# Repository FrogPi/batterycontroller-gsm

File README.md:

# GSM Battery Box Monitoring and Control Board

Electrial Engineering Final Year Project Deliverable

Charith Amarasinghe 2012 <ca508@ic.ac.uk>

## Features

* 1x Metered 12V Input/Output (Battery Connection)
* 2x Metered 12V Input/Outputs (Device Connection) with 4x IO pins each
* 1x 5V/3A USB Compliant Output
* Integrated SIMCOM SIM900 GSM Modem with U.FL Antenna Connector
* SPI interface for nRF24L01 RF module
* Integrated SIM and MicroSD socket
* RTCC Battery Backup
* PIC24FJ256GB106 Microcontroller with PICKit3 debug port
* microUSB OTG Port

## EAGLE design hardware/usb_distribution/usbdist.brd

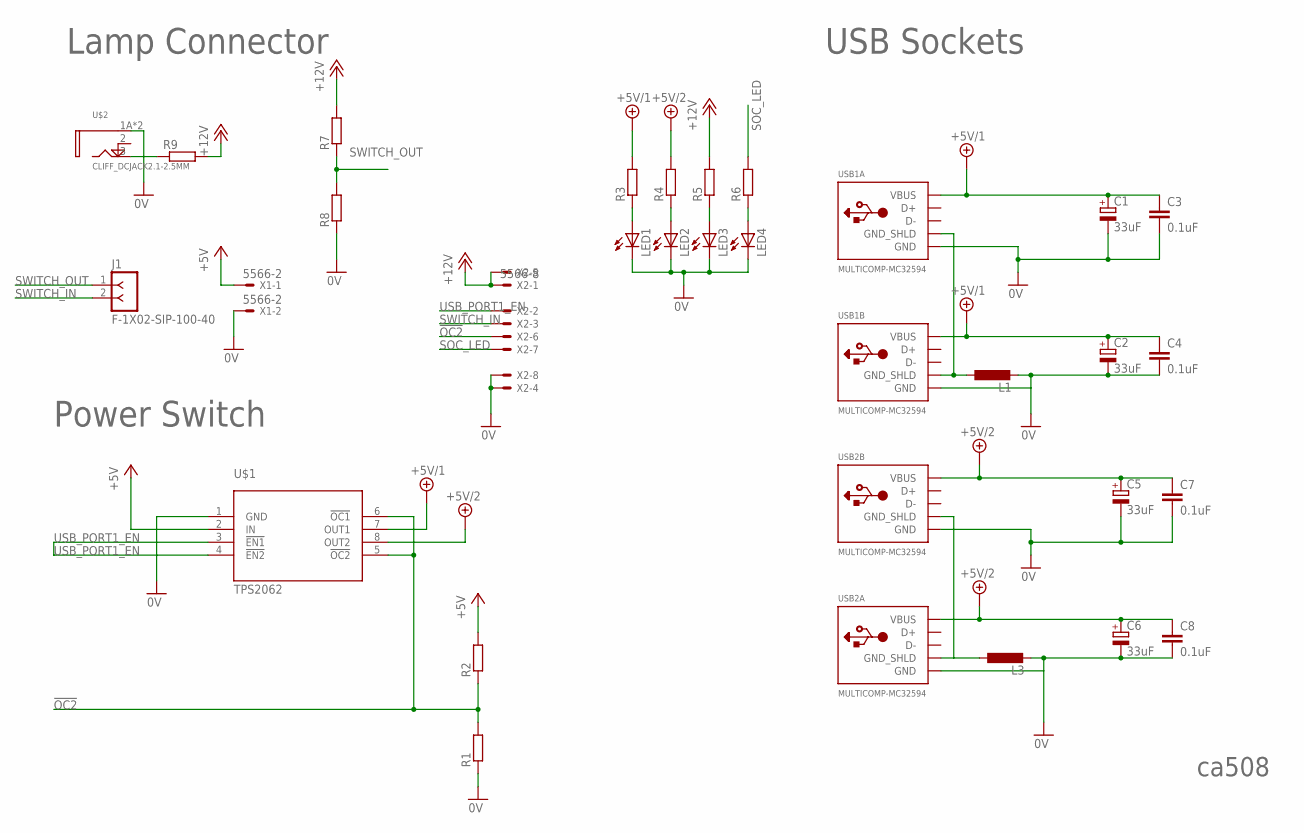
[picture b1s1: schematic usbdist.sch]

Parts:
C1, C2, C5, C6: 33uF; B/3528-21R; FARNELL 1672547
C3, C4, C7, C8: 0.1uF; C0603
J1: F-1X02-SIP-100-40; SIP-100-02-40
L1, L3: L-EUL2012C; L2012C
LED1, LED2, LED3, LED4: LEDCHIP-LED0805; CHIP-LED0805
R1, R2, R3, R4, R5, R6, R7, R8: R-EU_R0805; R0805
R9: R-EU_0204/5; 0204/5
U$1: TPS2062; SO8; FARNELL 1560652
U$2: CLIFF_DCJACK2.1-2.5MM; FC6814XS
USB1, USB2: MULTICOMP-MC32594; MC32594
X1: 5566-2
X2: 5566-8

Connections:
0V: C1.-, C2.-, C3.2, C4.2, C5.-, C6.-, C7.2, C8.2, L1.2, L3.2, LED1.C, LED2.C, LED3.C, LED4.C, R1.1, R8.1, U$1.1 (GND), U$2.1A (SLEEVE), U$2.1B (SLEEVE), USB1.USB1-4 (GND), USB1.USB2-4 (GND), USB2.USB1-4 (GND), USB2.USB2-4 (GND), X1.2, X2.4, X2.8
!OC2!: R1.2, R2.1, U$1.5 (!OC2!), U$1.6 (!OC1!), X2.6
+5V: R2.2, U$1.2 (IN), X1.1
+5V/1: C1.+, C2.+, C3.1, C4.1, R3.2, U$1.7 (OUT1), USB1.USB1-1 (VBUS), USB1.USB2-1 (VBUS)
+5V/2: C5.+, C6.+, C7.1, C8.1, R4.2, U$1.8 (OUT2), USB2.USB1-1 (VBUS), USB2.USB2-1 (VBUS)
+12V: R5.2, R7.2, R9.2, X2.1, X2.5
unnamed: L1.1, USB1.P$1 (GND_SHLD), USB1.P$2 (GND_SHLD), USB1.P$3 (GND_SHLD), USB1.P$4 (GND_SHLD)
unnamed: LED3.A, R5.1
unnamed: LED2.A, R4.1
unnamed: LED1.A, R3.1
unnamed: LED4.A, R6.1
unnamed: L3.1, USB2.P$1 (GND_SHLD), USB2.P$2 (GND_SHLD), USB2.P$3 (GND_SHLD), USB2.P$4 (GND_SHLD)
unnamed: R9.1, U$2.3 (TIP)
SHUNT: U$2.2 (SHUNT)
SOC_LED: R6.2, X2.7
SWITCH_IN: J1.2, X2.3
SWITCH_OUT: J1.1, R7.1, R8.2
USB_PORT1_EN: U$1.3 (!EN1!), U$1.4 (!EN2!), X2.2

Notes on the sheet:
Power Switch
Lamp Connector
USB Sockets
ca508

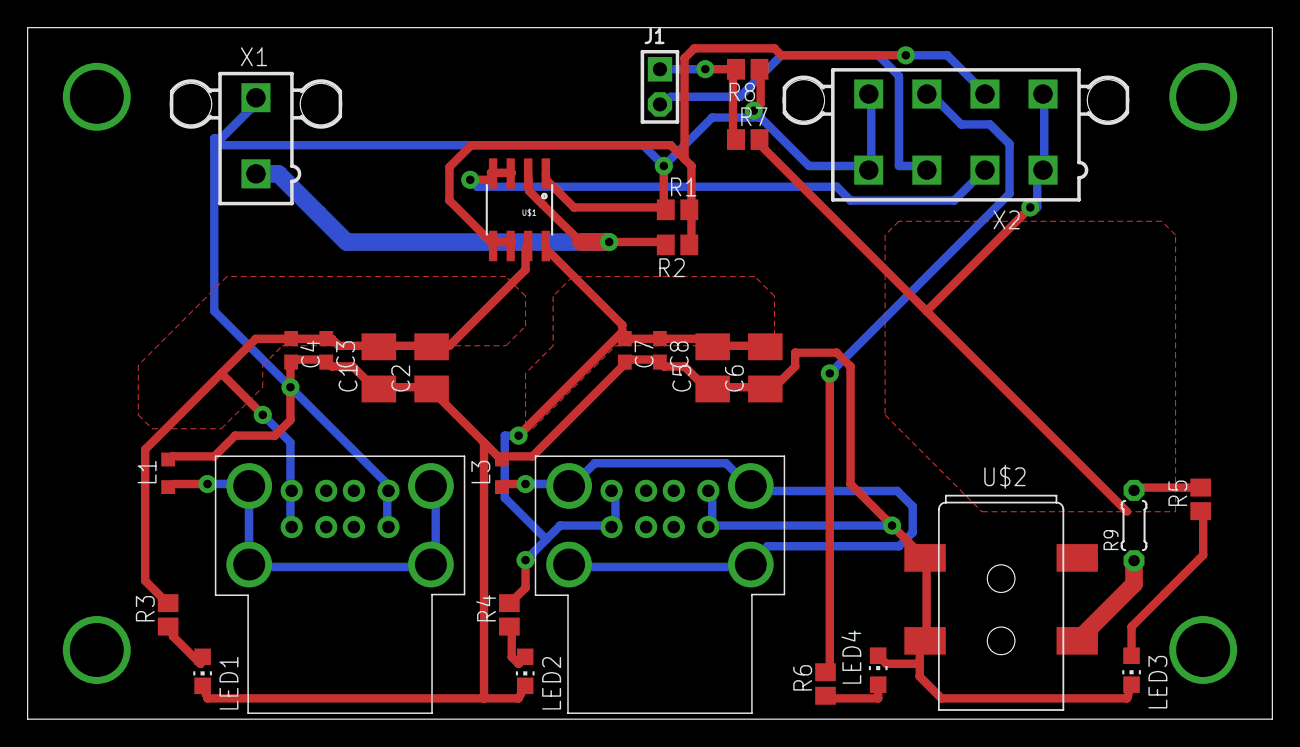
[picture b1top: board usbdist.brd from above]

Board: 2 copper layers, 90.0 x 50.0 mm, 30 parts (0 on the bottom side), 17 nets.

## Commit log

2012-11-14 Add licence information

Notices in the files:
parts and their libraries:
con-headers-jp: Copyright (C) 2008, Bob Starr
